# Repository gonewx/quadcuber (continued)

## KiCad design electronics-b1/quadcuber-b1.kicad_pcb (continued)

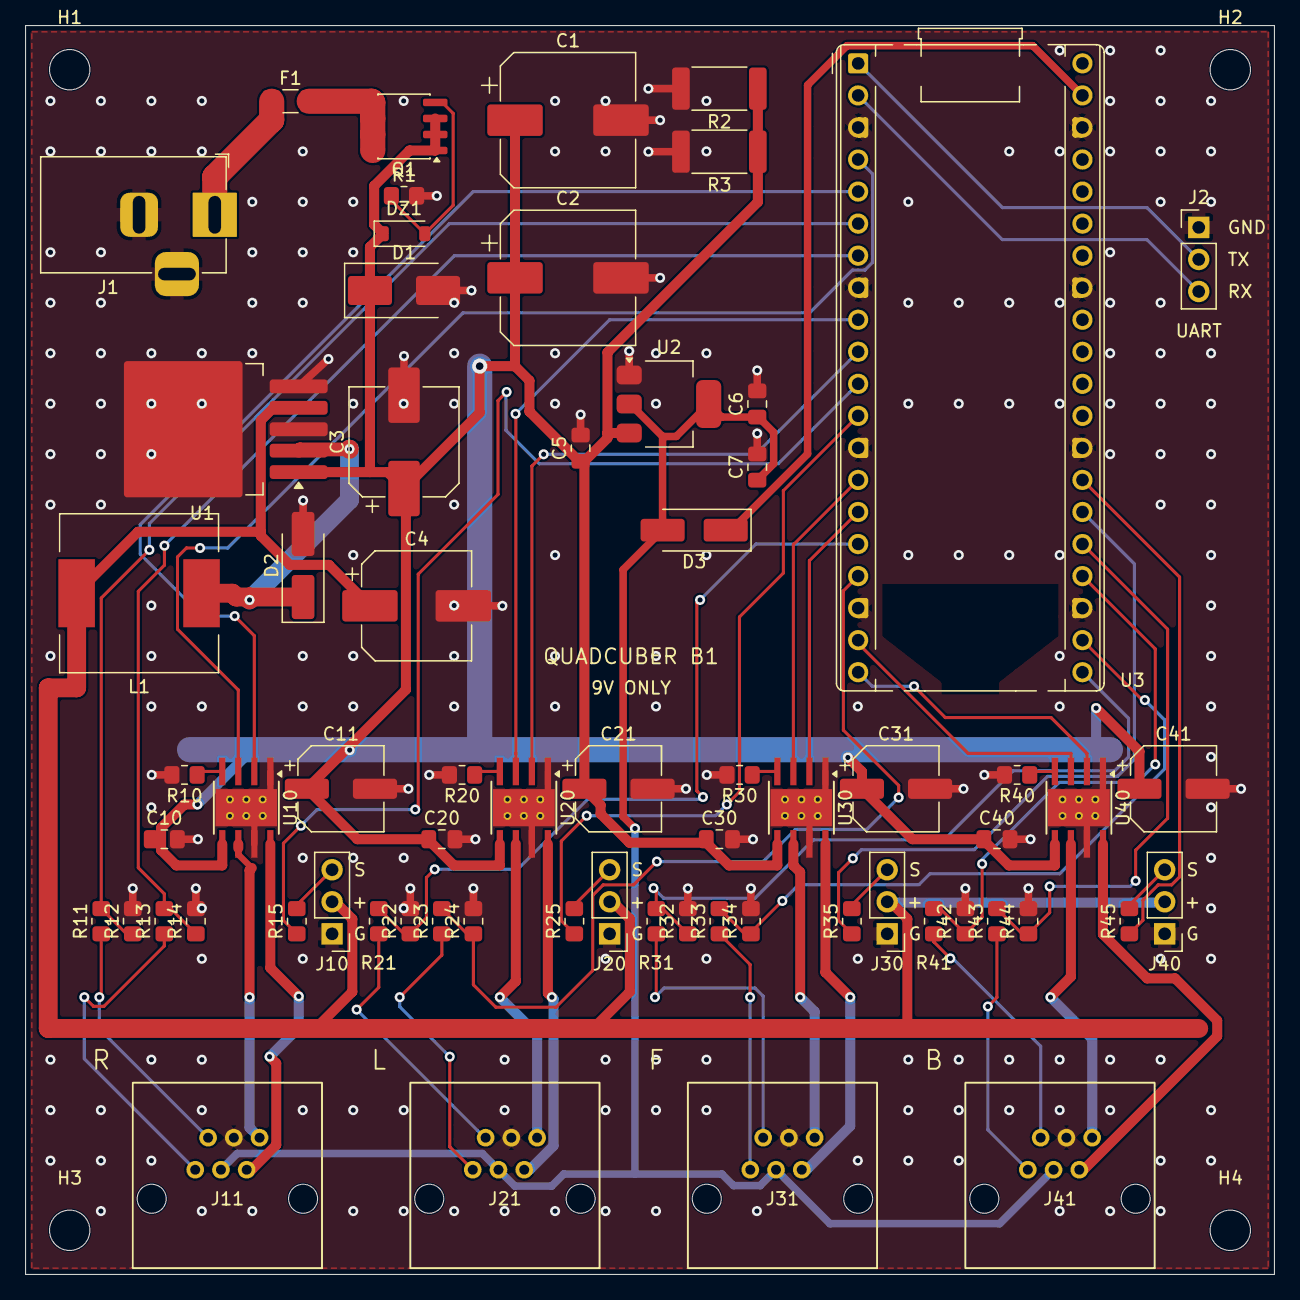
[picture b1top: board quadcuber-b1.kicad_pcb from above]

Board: 2 copper layers, 99.0 x 99.0 mm, 70 parts (0 on the bottom side), 55 nets.

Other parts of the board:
H1, H2, H3, H4: M3; MountingHole_3.2mm_M3

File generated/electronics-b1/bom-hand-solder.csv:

焊接顺序,类别,型号/规格,位号,数量,封装,说明
1,贴片 IC,AMS1117-5.0（SOT-223）,U2,1,SOT-223-3_TabPin2,输入最高 15V；约 0.1A 时功耗约 0.4W
1,贴片 IC,AO4407A P-MOS（-30V/12A，SOIC-8）,Q1,1,SOIC-8_3.9x4.9mm_P1.27mm,反接保护：漏极(5-8)接电源、源极(1-3)接 VM；导通后双向导电
1,贴片 IC,DRV8871DDAR,"U10,U20,U30,U40",4,Texas_HTSOP-8-1EP_3.9x4.9mm_P1.27mm_EP2.95x4.9mm_Mask2.4x3.1mm_ThermalVias,热风枪焊散热焊盘
1,贴片 IC,LM2596S-5.0（TO-263-5）,U1,1,TO-263-5_TabPin3,ON/OFF(5) 接地=常开；FB(4) 接输出；散热片焊盘接地铜
2,贴片电阻电容,0.1u 0.1µF 0805,"C7,C10,C20,C30,C40",5,C_0805_2012Metric_Pad1.18x1.45mm_HandSolder,
2,贴片电阻电容,10k 0805,"R1,R11,R13,R21,R23,R31,R33,R41,R43",9,R_0805_2012Metric_Pad1.20x1.40mm_HandSolder,
2,贴片电阻电容,10u/25V 10µF/25V 0805,C5,1,C_0805_2012Metric_Pad1.18x1.45mm_HandSolder,
2,贴片电阻电容,20k 0805,"R12,R14,R22,R24,R32,R34,R42,R44",8,R_0805_2012Metric_Pad1.20x1.40mm_HandSolder,
2,贴片电阻电容,220 0805,"R15,R25,R35,R45",4,R_0805_2012Metric_Pad1.20x1.40mm_HandSolder,
2,贴片电阻电容,22u/16V 22µF/16V 0805,C6,1,C_0805_2012Metric_Pad1.18x1.45mm_HandSolder,
2,贴片电阻电容,300R 1W 300Ω 1W 2512,"R2,R3",2,R_2512_6332Metric_Pad1.40x3.35mm_HandSolder,
2,贴片电阻电容,43.2kΩ 1% 0805,"R10,R20,R30,R40",4,R_0805_2012Metric_Pad1.20x1.40mm_HandSolder,限流约 1.48A（64/R）
3,贴片二极管,12V BZT52C12 稳压管,DZ1,1,D_SOD-123,阴极(1)接源极 VM，限制 |Vgs|<=12V
3,贴片二极管,SMBJ12A 单向 TVS,D1,1,D_SMB_Handsoldering,阴极(1)接 VM
3,贴片二极管,SS14 肖特基,D3,1,D_SMA_Handsoldering,阴极(1)接 Pico VSYS
3,贴片二极管,SS34 3A 肖特基,D2,1,D_SMA_Handsoldering,阴极(1)接开关节点
4,贴片保险丝,1206 贴片保险丝 8A 慢断,F1,1,Fuse_1206_3216Metric_Pad1.42x1.75mm_HandSolder,只防短路起火，不限流
5,贴片电解电容,100u/25V 100µF/25V 贴片电解 6.3×7.7,"C11,C21,C31,C41",4,CP_Elec_6.3x7.7,
5,贴片电解电容,220u/25V 220µF/25V 贴片电解 8×10.5（输入）,C3,1,CP_Elec_8x10.5,
5,贴片电解电容,470u/16V 470µF/16V 贴片电解 8×10.5（输出）,C4,1,CP_Elec_8x10.5,
5,贴片电解电容,470u/25V 470µF/25V 贴片电解 10×10.5,"C1,C2",2,CP_Elec_10x10.5,
6,贴片电感,33uH 3A 33µH/3A 贴片功率电感 12×12,L1,1,L_12x12mm_H8mm,
7,排针/排母,UART G TX RX 1×3 排针,J2,1,PinHeader_1x03_P2.54mm_Vertical,接 Zero W：GP0=TX、GP1=RX
7,排针/排母,树莓派 Pico H + 2×1×20 排母,U3,1,RaspberryPi_Pico_Common_THT,USB 朝上；排母两排相距 17.78mm
7,排针/排母,舵机 B S+G 1×3 排针,J40,1,PinHeader_1x03_P2.54mm_Vertical,自下而上 G/+/S
7,排针/排母,舵机 F S+G 1×3 排针,J30,1,PinHeader_1x03_P2.54mm_Vertical,自下而上 G/+/S
7,排针/排母,舵机 L S+G 1×3 排针,J20,1,PinHeader_1x03_P2.54mm_Vertical,自下而上 G/+/S
7,排针/排母,舵机 R S+G 1×3 排针,J10,1,PinHeader_1x03_P2.54mm_Vertical,自下而上 G/+/S
8,插座,9V DC 中心正 DC-005 5.5/2.1mm,J1,1,BarrelJack_Horizontal,脚1=中心(+)、脚2=外壳(-)、脚3=开关脚并地；焊前用实物核对孔位
8,插座,EV3 B 同批 EV3 插座（用户已有）,J41,1,EV3_Socket_UserDrawing,针序未用实物核实：接电机前断电六路通断
8,插座,EV3 F 同批 EV3 插座（用户已有）,J31,1,EV3_Socket_UserDrawing,针序未用实物核实：接电机前断电六路通断
8,插座,EV3 L 同批 EV3 插座（用户已有）,J21,1,EV3_Socket_UserDrawing,针序未用实物核实：接电机前断电六路通断
8,插座,EV3 R 同批 EV3 插座（用户已有）,J11,1,EV3_Socket_UserDrawing,针序未用实物核实：接电机前断电六路通断

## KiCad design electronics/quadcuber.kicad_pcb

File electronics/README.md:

# 四臂集成单板控制器 A1（板载RP2040） — 工程评审，未制造放行

> 当前手焊装配使用 [B1 底板](../electronics-b1/README.md)，请看 [B1 焊接与首次上电指南](../docs/b1-soldering-guide.md)。下文与本目录文件仅描述旧 A1 集成板，不适用于 B1。

本目录是 A1 电子源目录。打开 `quadcuber.kicad_pro`，包含原生可编辑原理图和四层 PCB、本地符号/封装库。本设计为**单块PCB，RP2040、QSPI Flash、晶振、USB-C、驱动和电源均直接焊接在板上**；A0的Pico H插装已移除。马达使用EV3裸插座。接线定义仍从 `../wiring/spec.py` 导入，固件未改动，也没有把 R/L 固件描述成已支持四臂控制。

**A1 历史工程首板入口：[送厂包与分工](../generated/electronics/engineering-first-board/README.md)。** 设计基线 `3cfff7c`（相对 `db20b98` 只把风险丝印改为 `PROTOTYPE` / `VERIFY EV3 PINMAP BEFORE MOTOR USE`）、J1为RASPC722X DC5521；嘉立创双面SMT共153件（J5含4个PTH屏蔽脚补焊待厂商确认），用户自焊18件通孔器件。39个型号已填LCSC编号；U7 W25Q16RVCNJQ与F10–F13 MF-MSMF110/16X-2未上架，须代购或寄料。本包供受控首板CAM审核，未宣称厂商已接受或量产/实板性能通过；提交时附CAM确认单。旧Phoenix与所有 `ENG-FULL-*` / `ENG-POWER-CONTROLLER-*` 文件只供历史审查，不得下单混用。

EV3仍以用户尺寸图及同批实物为依据，不索取不存在的完整MPN文件，不替换普通RJ12。首板承担孔位/主体适配返工风险；连接电机前必须做六路断电通断及机械试配，触点电流能力由受控实验建立。C26/C36不装。首次上电与逐级扩大负载条件见首板包，不要求首板尚未制出时已有实板动态测试结果。

## 已批准的BOOT与反馈修订

当前修订删除R20/R30，使100nF C22/C32直接跨接各自BOOT–SW；反馈保持100k/13.3k，改为RT0603BRD07100KL/RT0603BRD0713K3L（0.1%）。这是实物源电路、原理图、PCB、BOM和仿真输入的同步修改，旧49.9Ω仿真记录仅作为历史证据。[实施和验证记录](../generated/electronics/boot-direct-revision/README.md)保存布局改进、实际测试结果及未覆盖风险。未作量产性能放行；精度升级不等于已证明温漂及瞬态全程满足5.25V。工程首板的CAM入口与试验边界以上述唯一包为准。

## KiCad版本与显示

已使用用户批准的官方 **KiCad 10.0.7 Lite** 完成PCB与全部12张原理图的原生 `upgrade --force` 重存，以及ERC、含schematic parity的DRC和引脚契约复验。通过原生pcbnew API把原理图已有的MPN/Manufacturer同步为PCB隐藏字段，解决10版新增的198个缺失MPN一致性告警；未屏蔽检查。Lite本身缺少标准3D库；本轮已把实际使用的模型归档在工程内并以`${KIPRJMOD}`关联，171个已装配器件均有显示。蓝色插座主体和橙色110/16X保险是有来源的简化包络，F2/F3与L1/L2也采用按公开尺寸独立生成的简化包络（原厂CAD再分发许可未确认），不能称为整板精确3D验证；详见[显示修复报告](../generated/electronics/3d-display-repair/README.md)。C26/C36保持DNP并默认隐藏模型。

二维编辑器的红/褐色铜区和其他图层配色不是实物阻焊颜色。查看实物外观用“视图→3D查看器”（Alt+3）；成品绿色阻焊应在最终制造规格中明确。带Pico双排插座、丝印A0的板图是旧版；本目录A1采用直接焊接RP2040，打开时应核对丝印及工程路径。

## 交付入口

- [KiCad工程](quadcuber.kicad_pro)、[原理图PDF](../generated/electronics/schematic.pdf)
- [整板3D斜视](../generated/electronics/3d-display-repair/board-oblique.png)、[模型来源和限制](lib/3dmodels/README.md)、[当前显示修复核验](../generated/electronics/3d-display-repair/verification.json)
- [正面板图](../generated/electronics/pcb-top.png)、[反面铜图（顶视透视）](../generated/electronics/pcb-bottom.png)、[正面装配图](../generated/electronics/assembly.png)、[反面装配图（顶视透视）](../generated/electronics/assembly-bottom.png)
- [汇总电子BOM](../generated/electronics/bom-grouped.csv)、[逐件BOM](../generated/electronics/bom.csv)、[贴装坐标](../generated/electronics/positions.csv)
- [ERC](../generated/electronics/erc.rpt)、[DRC](../generated/electronics/drc.rpt)、[状态与源哈希](../generated/electronics/release-status.json)、[独立复核](../generated/electronics/independent-review.md)
- [唯一工程首板Gerber/钻孔、SMT BOM/CPL、自焊清单与CAM单](../generated/electronics/engineering-first-board/README.md)。旧 `fabrication-preview-NOT-RELEASED` 为原始审核输出，不单独作为订单交付。

正反面SVG/PNG沿同一KiCad顶视坐标系绘制，便于对照；实际从板底观察时需镜像，不可用透视图推断插座针序。

TP测试焊盘和安装孔是PCB内建特征，采购数量记为0；可选电容的DNP原因单独列在BOM备注中。

## 电源仿真状态

已保留[65个简化ngspice边界工况及热敏感性计算](simulation/README.md)，以及[108个保护/RLC/能量工况](../generated/electronics/protection-analysis/report.md)。它们不等于芯片动态验证。本轮已取得TI未加密TPS54302原厂模型，执行9个真实双路BOM输入/电容工况，但均在0.458～0.779ms因数值问题中止，**0个完整完成、0个通过，负载阶跃尚未执行到**。见[原厂模型报告、部分波形与日志](../generated/electronics/simulation/buck-vendor/report.md)。当前阻塞已从下载变为ngspice动态兼容；制造HOLD保持。[确切料号审查](sources/bom-exact-part-audit.md)仍记录原厂已核与未决项。

## BOM选型标准

同等电气、散热、供应与装配条件下，**默认优先贴片元件**，以缩短回路、降低高度并便于机器装配。先核确切原厂料号、封装/引脚、生命周期，再按实效电容、脉冲能量、持续/RMS电流及局部温升留余量；不能用芯片峰值额定充当整板持续额定。常用低功耗器件优先0603/0805，小封装只在布线/去耦确有必要时使用，功率器件按载流与散热选择尺寸。

连接器优先兼容、插拔固定及足够触点电流；大电容同时比较容量、纹波、寿命、体积和高度，不能只因“贴片”而牺牲性能。当前大多数器件已是贴片，大电解/布局仍可研究紧凑化；144×112mm是当前工程版外形，**并未证明已优化到最小**。本轮保持机械外形，先完成确切料号与保护闭环。原厂已核、渠道生命周期和仍未知的证据层级见[完整BOM审查](sources/bom-exact-part-audit.md)。

## 架构与器件

- **控制器：裸RP2040 QFN56+EP**。保留GPIO0～21、8个PIO状态机、12MHz时钟、2MiB Flash以及GP25指示灯，使用基于RPI_PICO的QUADCUBER_A1 MicroPython UF2，无需迁移MCU平台。GP22/23/26～29未用；GP24为USB VBUS分压检测。ROM BOOTSEL、RUN复位、UART和SWD均直接引出；SWD口3V3为参考电压，禁止外部注入供电。
- **Flash：W25Q16RVCNJQ**，CN 150mil SOP8，原厂在产替代，保留3.9mm窄体焊盘。使用[QUADCUBER_A1启动配置](firmware/README.md)，在现有MicroPython/Pico启动代码上修正QE位判断，避免RV状态寄存器差异造成反复写入；仍通过USB UF2烧录。选型、供货及逐命令兼容证据见[Flash复核](sources/flash-selection-review.md)。
- **12MHz ABM8-272-T3**，CL10pF、两颗15pF、XOUT串1k；RP2040每个电源脚配置100nF，内部稳压输入/输出各1µF。3.3V接IOVDD/ADC_AVDD/VREG_IN/USB_VDD；VREG_OUT仅接1.1V DVDD，TESTEN及EP接地。
- **USB4105-GF-A** USB-C USB2从设备，CC1/CC2各独立5.1k，下游数据通过USBLC6-2SC6和27Ω串阻。GCT原厂图与库的定位孔、壳脚槽和针序逐项核对；没有USB PD，也不向主机提供VBUS。

- **四路 DRV8871DDAR**，每马达一颗，HTSOP-8 PowerPAD，热焊盘接地、有原厂推荐热孔。IN1/IN2 真值表与现有慢衰减 PWM 一致，00滑行/休眠、01反转、10正转、11刹车。现有20 kHz PWM符合器件范围；休眠后首次唤醒最多50 µs，样机须重测低速定位。不沿用 DRV8833 名义模块电流：DRV8833 PWP/RTY 每桥1.5 A RMS，而PW只有0.5 A，且10.8 V推荐上限不利于9 V母线回灌。DRV8871的6.5～45 V供电裕量更合适，**3.6 A只是峰值，不是整板持续额定**。
- 每桥 **43.2 kΩ ±1%**，64 kV/R 名义1.481 A；按59～69 kV及电阻容差推算1.352～1.613 A。该门限不是所有PWM/电感工况下的精密峰值保证。9 V EV3大马达原厂堵转1.8 A，因此设计有意限流降低堵转扭矩，带载夹持须验证。
- **两路 TPS54302DDCR**，5 V基准电路，R上100k/下13.3k、10µH电感、双22µF/25V输出及75pF前馈（C26/C36可选470µF默认DNP，须验证环路后才装）。每路带两个舵机，A路还带编码器与RP2040。电感 **SRP1245A-100M** 为10µH、9 A RMS、16 A饱和额定，避免饱和电流低于控制器6 A故障限流上界。芯片3 A额定不等于封闭机箱持续3 A；设计负载预算见下。
- **八路 SN74LVC2G17 施密特整形**：每输入1k串联、100k下拉，5 V容限、3.3 V供电。替代旧10k/20k分压，避免5 V边缘直接到RP2040；不反相、保持`ENC_PULLUP=False`，PIO资源不变。器件Ioff保证断电输出不会把编码器5 V送入3.3V供电。马达pin4由独立0.5 A PTC保护的5V_ENC供电。
- 舵机每路**MF-MSMF110/16X-2、16 V、1.1 A PTC**（替代已淘汰6 V旧型号）、**SN74AHCT1G125**（由该路PTC后供电）、220Ω输出串阻、GPIO及输出下拉。3.3 V输入符合TTL阈值；原厂输入漏电在VCC=0时也有规格，避免USB-only的高GPIO经舵机信号反向供电。此处不声称输出端可任意外灌电压；不接外部5 V到舵机端口。

## 电源、回灌与默认态

J1采用 **Switchcraft RASPC722X**，配5.5/2.1 mm中心正插头（官方配762/762Z、筒长9.5 mm），只接**稳压9 V ±2%直流电源**，设计以≤5 A首板连续输入预算、8 A入口保险为边界。sleeve shunt不接线；推荐三槽孔、父线程图面核验来源及原件待归档状态见[入口候选审查](sources/raspc722x-review.md)。厂家5 A carrying额定不取代首板连续温升验证，8 A保险不构成5 A限流。不能接12 V，也不能接未评估的3串锂电。外部电源应有限流功能，动力断开应通过入口物理开关/拔电；USB仅用于逻辑和烧录，不能带动电机、舵机。

入口为已纠正的**0407008.WR、8 A/24 VDC时滞保险**（407系列，1206专用焊盘）、LM74700QDBVRQ1+CSD18540Q5B理想二极管。MOS源极接VIN_FUSED、漏极及大焊盘接VM；LM74700的VCAP电容跨VCAP和ANODE，不能误接到地。保护反极性、阻止VM倒流到电源，避免串联肖特基8 A时约4.26 W的发热。**EN不是正向断电开关**，体二极管仍可供电；该电路也没有浪涌限流。

输入SMBJ12CA吸收正负瞬态，输出SMBJ12A吸收回灌脉冲。输出TVS的12 V是反向工作电压，不是钳位电压；额定脉冲钳位19.9 V，相对于驱动45 V、降压28 V和VM电容25 V有裕量，但必须实测布线寄生尖峰。TVS不适合持续消耗制动功率，也不保护电机不受任何过压：只允许9 V供电，禁止持续外力反拖。控制应以慢衰减刹车优先，回灌测试必须观察VM、电机端、电源端与TVS温升。

母线六只470µF/25 V共2820µF，储能9→12 V约0.0888 J，9→13.3 V约0.135 J；它不是四马达机械动能的保证。新增R500/R501，两只300Ω/1W并联为150Ω母线泄放，9.18 V时总耗散约0.562 W，给重复小能量回灌提供确定的放电路径。暂定**整板每次回到母线的总能量≤0.05 J、频率≤5 Hz、脉宽5～100 ms**，此范围的简化模型最高VM11.204 V且不进入TVS雪崩；实际机械能仍须验证。该泄放不是大功率制动器，也不允许持续反拖。首次上电和热插拔也要核验电容浪涌与保险I²t。F1名义熔断I²t为24.12 A²s，不是保证最小值或总开断能量；分断能力60 A@24 VDC，不能用于无限短路容量的电池。时滞保险不保护半导体快速故障，外部9 V电源必须具备短路限流。没有把旧R空载实测当作这块新驱动板的试验结果。

5V_A经D2（SS14），USB VBUS经F3（0.5A PTC）和D5（SS14），分别单向汇入VSYS，再由TLV75533PDBVR产生3.3V。两路源的阳极独立、阴极均接VSYS，外部5V不能直接进入USB VBUS。USBLC6的上保护轨接VSYS、就近100nF，避免外供电时DP上拉经ESD导向二极管绕过D5回灌VBUS。所有GND共地，USB地不承担动力回流。

GP24的100k/100k分压用于遥测。Stock TinyUSB通常强制认为VBUS存在，分压本身不会关闭USB上拉；断电主机的数据脚输入保护路径尚须验证，因此不声称通过USB规范或零微安回流认证。首板须分别测VBUS及DP/DM对断电主机的电压/电流。USB仅给逻辑供电，F3不构成USB枚举电流协商。

TLV755的500mA是芯片额定，本板逻辑3.3V连续预算≤150mA。DBV封装按TI给出的231.1°C/W估算：VSYS约4.7V、150mA时0.21W、约49°C温升，40°C环境约89°C结温；这只是估算，首板必须测满负载与最高环境温度，不能套用其他封装的热阻。

输入下拉令RP2040未启动/复位时电机00、舵机无脉冲。供电瞬态下舵机内部仍可能抖动，PTC不会瞬时切断精确电流，驱动自动热恢复也不是锁存式急停。固件原有未标定锁定保持不变。

## 负载与热边界

四电机同时到名义限流约5.92 A；四只灰色270°Geekservo原厂标称堵转各700mA，总2.8 A@5 V（原厂没有给测试电压和容差，不是保证上限）。另按逻辑/编码器0.25 A@5 V、降压效率85%估算，输入约7.91 A，已经接近8 A保险，**不允许把全堵转当持续工作模式**。设计正常工况预算：马达各≤0.75 A RMS作为首板热验证目标、两个5 V支路各≤1.5 A持续（A路包含逻辑预算），两路5 V同时1.5 A时加泄放负载合计约5.02 A，需稍降负载以满足入口≤5 A；短时峰值和温升须实测。PTC1.1 A是25°C保持电流，热环境下降额，不能用它来承诺舵机启动上限。

DRV8871在1 A时以0.565Ω典型桥阻估算0.565 W；升温后桥阻上升，1.48 A时仅导通损耗即约1.24 W。TI 41.1 K/W是规定测试板结果，不能直接当本板热阻。每颗留独立散热区域，热焊盘/热孔/地铜必须焊接完整；环境40°C下目标结温<125°C，需同时四路负载热测确认。若达不到，应降连续电流/占空比或增加散热，不能提高限流电阻之外的额定宣传。

入口J1→F1→Q1源极设宽铜区，Q1漏极以12颗Ø0.4 mm过孔连接VM内平面。DRV每颗6个原封装热孔接地，VM及PGND增加并联过孔；上下层地铜与内层地面共同散热。实际铜区需结合样机温升核验，不把理想走线公式当额定。两颗主输入10µF置于降压芯片背面近旁，以0.8 mm短线接邻近VIN/GND孔，最长1.956 mm；记录见`buck-loop.json`。

## 板形、装配与机械安装

144×112 mm矩形，四个Ø3.2 NPTH孔，坐标(4,4)、(140,4)、(4,108)、(140,108)，孔距136×104 mm均为8 mm网格。四个34 mm臂单元（J10为避开左安装孔额外右移1 mm）容纳12.2×15 mm插座主体和至少15.3 mm固定耳预留宽度、直插线缆、舵机排针、驱动散热区；上部为USB-C及板载RP2040最小系统、两套降压和电源入口。小于这一宽度会挤占接口及功率单元余量，因此没有沿用洞洞板尺寸。

它不是直接卡入现有乐高销孔的板。通过**新增绝缘托架**底挂，主要元件面朝下，反面（含C20/C30输入电容、RP2040去耦及USB供电二极管）基板表面置于模型Y=124 mm；X/Z以机器人中心为板中心。LDraw Y朝下，模型全机最大Y=116 mm；独立审查扫描臂0..355°每5°及开/合两端、支承0/20.4/40.8 mm，下方8 mm空隙成立。**这只证明裸基板与模型分离，不证明托架、反面电容、紧固件、线缆或公差完成安装验证**。

**双面装配**：C20/C30、RP2040去耦和USB供电D5等位于B.Cu；反面朝机器人，必须从8 mm净距中扣除反面最高器件的实际最大高度、焊脚及装配公差，不能把8 mm称为器件净空。最终双面装配以`positions.csv`的Side列及反面装配图为准。

需新增足够高度的脚及底部防护，按最高电容、双面器件高度、焊脚剪切和至少5 mm防护空隙确定，初始为板上方8 mm、板下约25 mm及防护的40 mm级抬高预算。托架机械设计未冻结，因此不能声称机械集成已完成。USB一侧留至少15 mm插拔空间，马达口外预留25 mm直出区再弯线，按实际线材弯曲半径调整；不将未确认的线长写成BOM事实。舵机口丝印G/+ /S，**棕/黑GND，中间红+5 V，信号S**；排针本身无防呆，插前按实际线序确认。

## 重建与编辑

已安装/使用官方KiCad 10.0.7 Lite和其Python 3.11 pcbnew；外部布线工具从[Freerouting官方v2.1.0发布](https://github.com/freerouting/freerouting/releases/tag/v2.1.0)下载。无需购买模块、运行云端EDA或迁移固件。

```sh
# 如环境HOME只读，可把XDG配置/缓存指向可写临时目录（build.py已自动处理）。
export XDG_CONFIG_HOME=/tmp/quadcuber-kicad/config
export XDG_CACHE_HOME=/tmp/quadcuber-kicad/cache
export XDG_DATA_HOME=/tmp/quadcuber-kicad/data
# 本环境的官方Lite AppImage解包入口；其他安装可改为自己的路径。
export KICAD_APP_RUN=/workspace/tools/kicad-10.0.7/squashfs-root/AppRun
# 或分别设置KICAD_CLI（可执行文件路径）和KICAD_PYTHON（Python命令，可含参数）。
# 普通系统安装不设上述变量：使用PATH内kicad-cli和当前Python。
# CLI及pcbnew均须为10.0.7，版本不符立即报错。
# 正常编辑：直接用KiCad编辑原理图/PCB，再导出验证。
python3 electronics/build.py
python3 electronics/check.py
# 对比冻结的迁移前基线与当前板的几何/网表（不修改设计）。
"$KICAD_APP_RUN" python3.11 electronics/verify_kicad10_migration.py
python tools/build_distribution.py
python -m unittest tests.test_wiring tests.test_arm_selection tests.test_firmware tests.test_repository_layout -q

# 仅重建原理图/BOM，不动已布线PCB：
/usr/bin/python3 electronics/generate.py --metadata-only
# 从零研究布局才运行以下命令；它会覆盖已布线PCB，并不重现最终走线。
/usr/bin/python3 electronics/generate.py
```

`build.py`使用现存KiCad源，不会重置布局。标准输出唯一位于`generated/electronics/`：BOM、网表、SVG/PDF原理图、板图、ERC/DRC、制造预览文件、审查状态。`generate.py`与`circuit.json`中的坐标是初始布局，最终位置和双面装配以native PCB及其导出的`positions.csv`为准。自动布线结果可能不同，控制器由update_controller.py重新放置背面去耦并建立In2局部3V3岛；其操作会删除该区域走线，不能当普通导出步骤。控制器细间距扇出、去耦朝向和局部地回流已在native PCB中进一步修正；辅助布局脚本仅用于重新研究布局。In1始终保留完整地参考，In2只在控制器局部允许少量信号与1.1V出线，VM功率区不作信号通道。后处理脚本含历史A0特定废线清理；重新布线后必须重新审查并修正，而不是保证一键得到相同铜形。只有native PCB是最终布线事实；`generate.py`保存可重做初始布局的方法，不承诺重现自动布线每个拐点。

## 实际验证记录

本次正式导出：ERC 0错误/0警告；包含原理图一致性检查的DRC 0违规、0未连接、0封装错误；543个已连接符号引脚与PCB的网络契约核对为0错误。报告和源哈希见交付入口。历史独立审查`generated/electronics/independent-review.md`绑定迁移前KiCad 9 PCB哈希，不能作为当前10版文件已被重新独立审查的证明。当前迁移证据见`generated/electronics/kicad10-migration.json`及本次重新导出的报告；迁移前后器件位置、焊盘尺寸/钻孔/网络、走线与过孔、铜区轮廓和实填铜、板框均相同。J5两个无编号NPTH的层掩码由10版原生保存规范化为全部铜层（孔位与孔径不变），物理几何比较明确归一此项。本次再次执行既有接线/R-L选择/固件与仓库布局回归；按仓库命令`python tools/build_distribution.py`补建分发产物后，相关51项与仓库布局8项合计**59项全部通过**，没有修改测试断言；这不等同四臂软件或PCB实物通过。

## 放行清单

1. **EV3实物针序与项目工作边界**：孔位及1/6标注已按用户图落实；不再索要不存在的更多资料。完整EV3板制板前仅需同批样品一次六路断电通断记录及观察方向，避免镜像/错序；触点电流、压降、温升与机械试配在受控样板上建立限定边界，不冒充厂家额定。如映射改变，更新封装网络并重跑ERC/DRC。NO-EV3台架变体单独标识，不替代完整设计。
2. **电源/热原型**：9 V台式电源限流，从无马达到单路负载再四路，测5 V启动、负载跃变、编码器波形和20 kHz电机电流；禁长时堵转。验证TVS能量、VM瞬态、铜温、驱动结温估算、输入保险及PTC降额。
3. **控制器与USB组合**：首次按住BOOTSEL插USB，确认ROM盘枚举及QUADCUBER_A1 UF2刷写；RUN复位、SWD读写、12MHz时钟、1.1/3.3V启动、QSPI读写及编码器/舵机默认态。USB-only、9V-only、两者同时、动力掉电/恢复，确认无反向供电、复位失控或异常舵机脉冲。
4. **机械**：托架与脚、USB/马达插拔、线缆运动包络、反面绝缘、安装螺钉不触铜、USB插头与BOOTSEL/RUN按键可达性。
5. **制造**：板厂确认4层1.6 mm，外铜2 oz/内铜1 oz，RP2040细间距和USB差分阻抗需板厂复核，逻辑最小0.15 mm线宽/间距（其余网络0.20 mm），USB连接器原厂孔到焊盘间隙按专用0.18 mm规则，最小0.30 mm成品孔；驱动热孔工艺和锡膏分窗按TI，检查焊孔与排针实际料样。当前没有做过PCB实物测试。

## 资料与许可证

详细依据见 `sources.md`。本地拷贝KiCad标准封装来自本环境KiCad9库，遵守[KiCad Libraries License](https://www.kicad.org/libraries/license/)的CC-BY-SA4.0及PCB设计例外；RP2040封装保留原厂焊盘并将EP热孔改为Ø0.30/焊盘Ø0.60 mm，以匹配板厂工艺；EV3自建封装明确标注未核部分。不把公开资料的缺失字段编造成制造商规格。

旧 `python electronics/package_review.py` 仅生成历史审查汇总到 `output/electronics/`，会包含历史变体，不能用作当前送厂资料。当前首板只能使用 [engineering-first-board 唯一入口](../generated/electronics/engineering-first-board/README.md)，由 `electronics/package_first_board.py` 生成并校验源哈希。

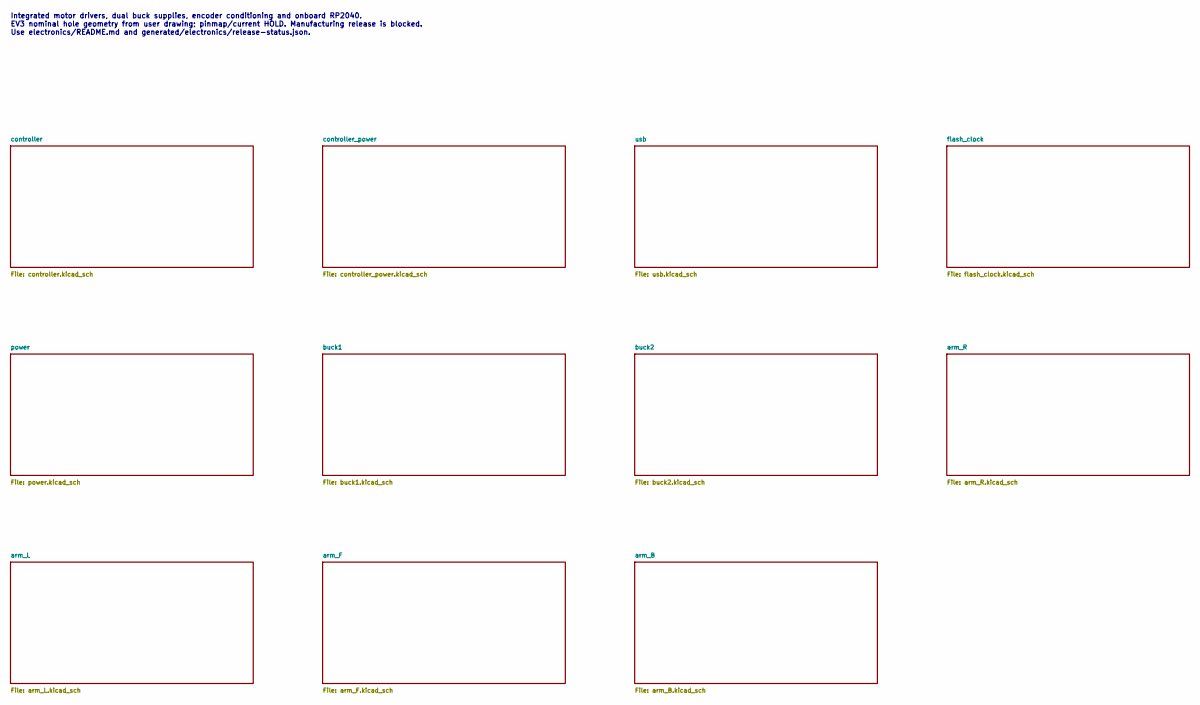
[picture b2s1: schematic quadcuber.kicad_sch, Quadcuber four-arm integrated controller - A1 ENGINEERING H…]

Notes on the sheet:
Integrated motor drivers, dual buck supplies, encoder conditioning and onboard RP2040. EV3 nominal hole geometry from user drawing; pinmap/current HOLD. Manufacturing release is blocked. Use electronics/README.md and generated/electronics/release-status.json.

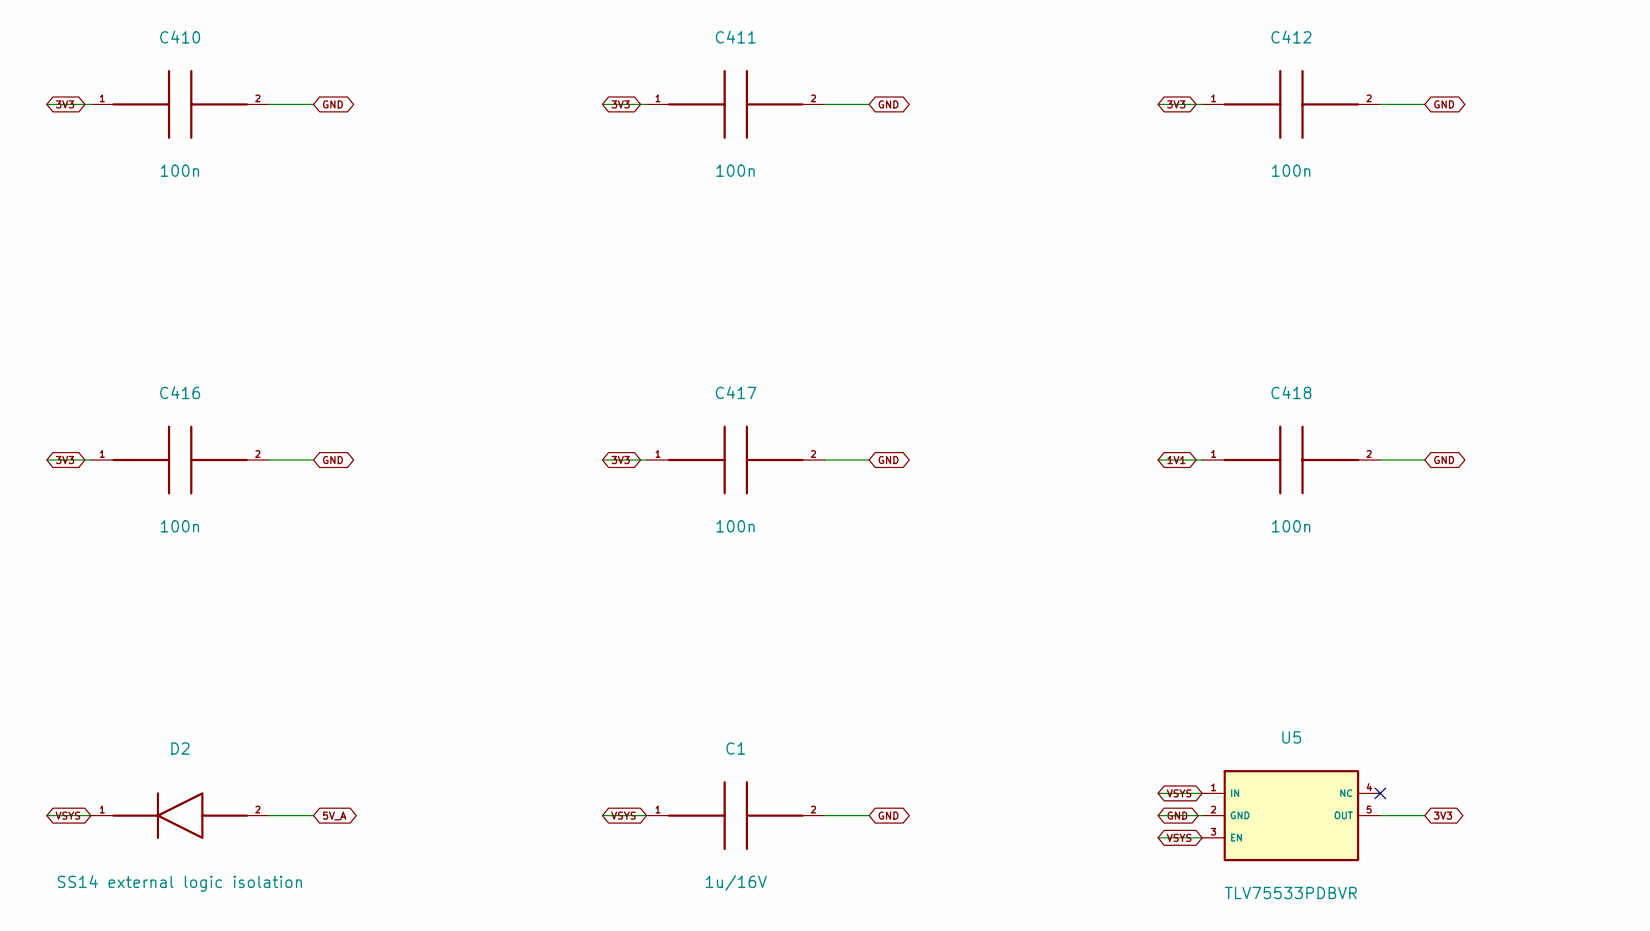
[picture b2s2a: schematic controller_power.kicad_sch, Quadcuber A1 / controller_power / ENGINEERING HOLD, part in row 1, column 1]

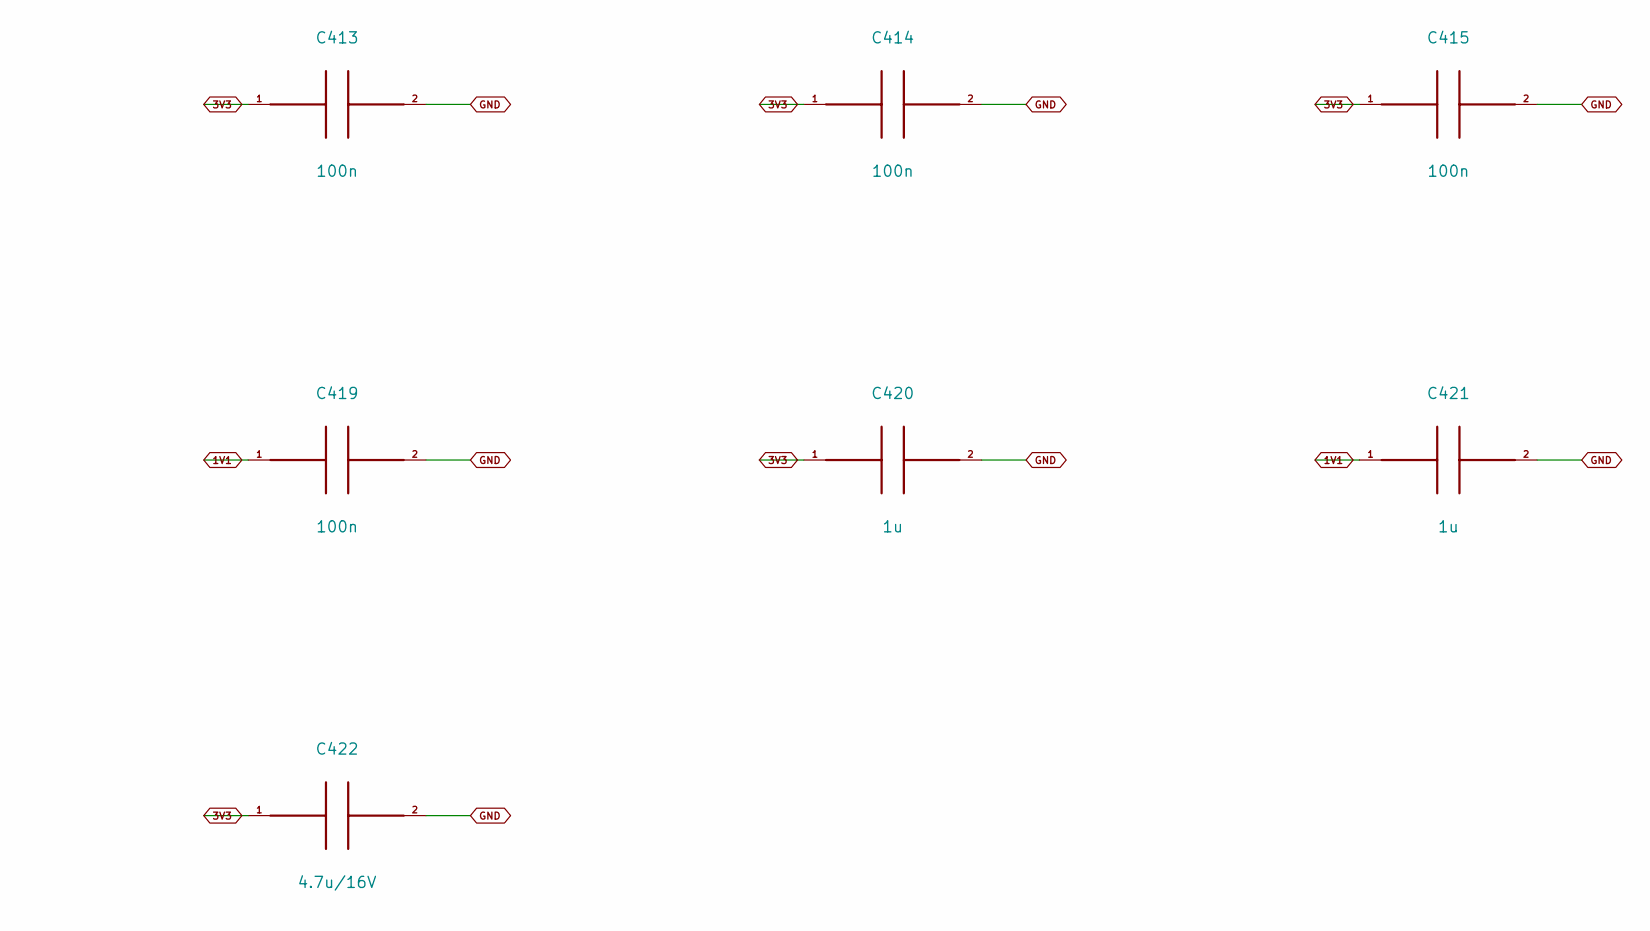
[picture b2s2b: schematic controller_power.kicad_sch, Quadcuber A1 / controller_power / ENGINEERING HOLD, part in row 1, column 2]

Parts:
C1: 1u/16V; C_0805_2012Metric; MPN GRM21BR71C105KA01L
C410, C411, C412, C413, C414, C415, C416, C417, C418, C419: 100n; C_0402_1005Metric; MPN GRM155R71C104KA88D
C420, C421: 1u; C_0402_1005Metric; MPN GRM155R61C105KA12D
C422: 4.7u/16V; C_0805_2012Metric; MPN C0805C475K4PACTU
D2: SS14 external logic isolation; D_SMA; MPN SS14-E3/61T
U5: TLV75533PDBVR; SOT-23-5; MPN TLV75533PDBVR

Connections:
1V1: C418.1, C419.1, C421.1; also elsewhere on the board
3V3: C410.1, C411.1, C412.1, C413.1, C414.1, C415.1, C416.1, C417.1, C420.1, C422.1, U5.5 (OUT); also elsewhere on the board
5V_A: D2.2 (A); also elsewhere on the board
GND: C1.2, C410.2, C411.2, C412.2, C413.2, C414.2, C415.2, C416.2, C417.2, C418.2, C419.2, C420.2, C421.2, C422.2, U5.2 (GND); also elsewhere on the board
VSYS: C1.1, D2.1 (K), U5.1 (IN), U5.3 (EN); also elsewhere on the board

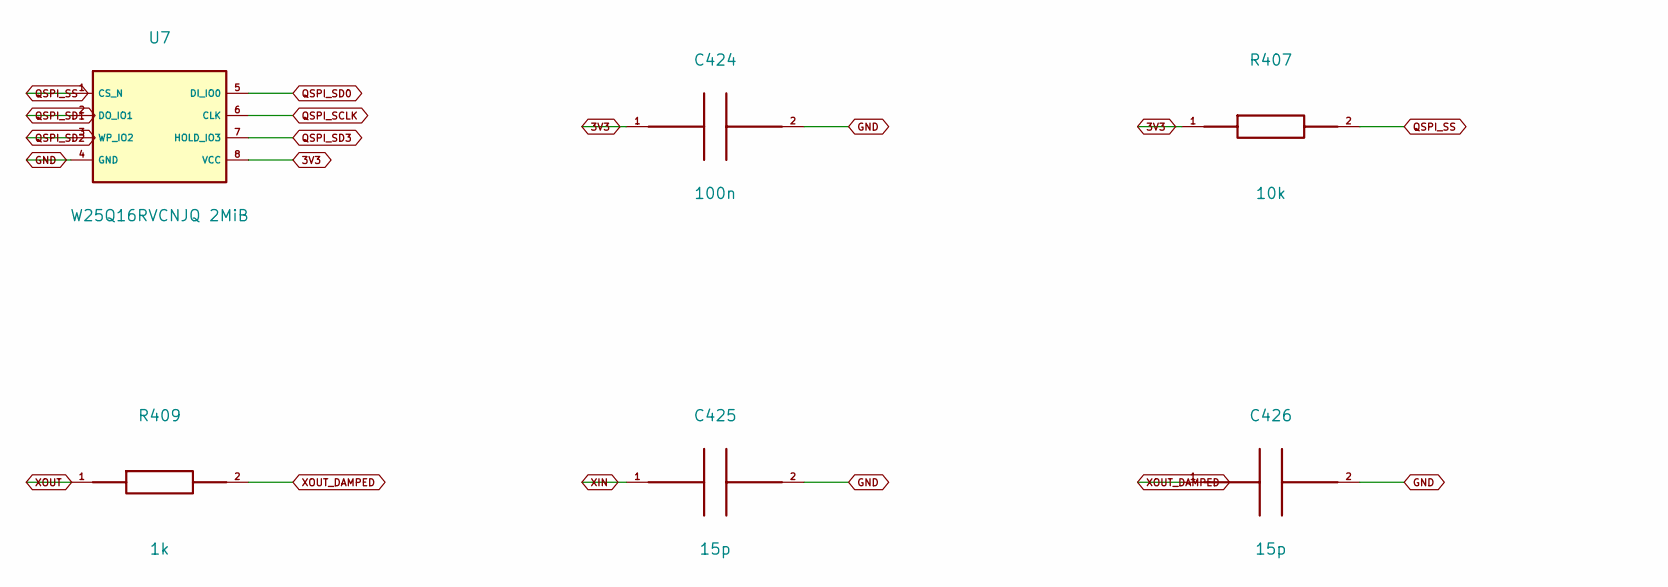
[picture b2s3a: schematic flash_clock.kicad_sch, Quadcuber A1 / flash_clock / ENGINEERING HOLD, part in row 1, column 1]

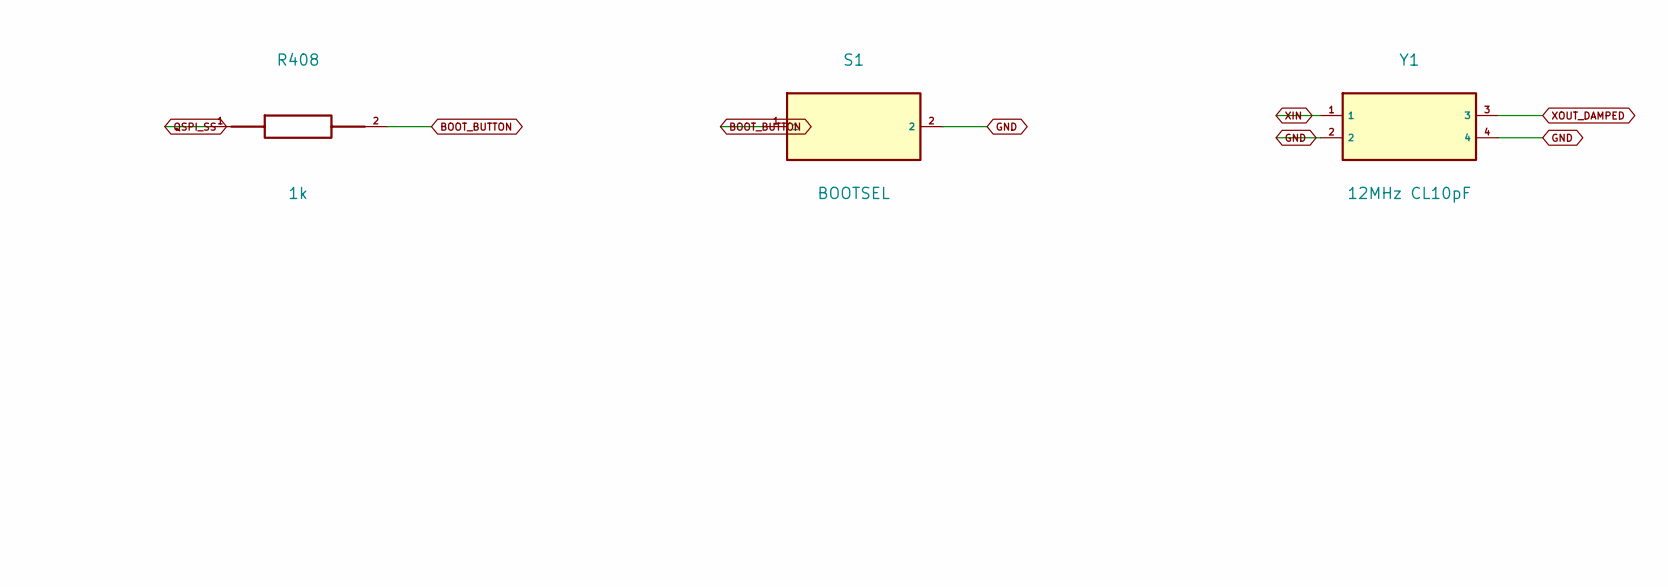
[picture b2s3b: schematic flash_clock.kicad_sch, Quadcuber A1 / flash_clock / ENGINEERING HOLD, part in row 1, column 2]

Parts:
C424: 100n; C_0402_1005Metric; MPN GRM155R71C104KA88D
C425, C426: 15p; C_0402_1005Metric; MPN GRM1555C1H150JA01D
R407: 10k; R_0603_1608Metric; MPN RC0603FR-0710KL
R408: 1k; R_0603_1608Metric; MPN RC0603FR-071KL
R409: 1k; R_0402_1005Metric; MPN RC0402FR-071KL
S1: BOOTSEL; SW_SPST_TL3342; MPN TL3342F160QG
U7: W25Q16RVCNJQ 2MiB; SOIC-8_3.9x4.9mm_P1.27mm; MPN W25Q16RVCNJQ
Y1: 12MHz CL10pF; Crystal_SMD_3225-4Pin_3.2x2.5mm; MPN ABM8-272-T3

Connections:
3V3: C424.1, R407.1, U7.8 (VCC); also elsewhere on the board
BOOT_BUTTON: R408.2, S1.1
GND: C424.2, C425.2, C426.2, S1.2, U7.4 (GND), Y1.2, Y1.4; also elsewhere on the board
QSPI_SCLK: U7.6 (CLK); also elsewhere on the board
QSPI_SD0: U7.5 (DI_IO0); also elsewhere on the board
QSPI_SD1: U7.2 (DO_IO1); also elsewhere on the board
QSPI_SD2: U7.3 (WP_IO2); also elsewhere on the board
QSPI_SD3: U7.7 (HOLD_IO3); also elsewhere on the board
QSPI_SS: R407.2, R408.1, U7.1 (CS_N); also elsewhere on the board
XIN: C425.1, Y1.1; also elsewhere on the board
XOUT: R409.1; also elsewhere on the board
XOUT_DAMPED: C426.1, R409.2, Y1.3

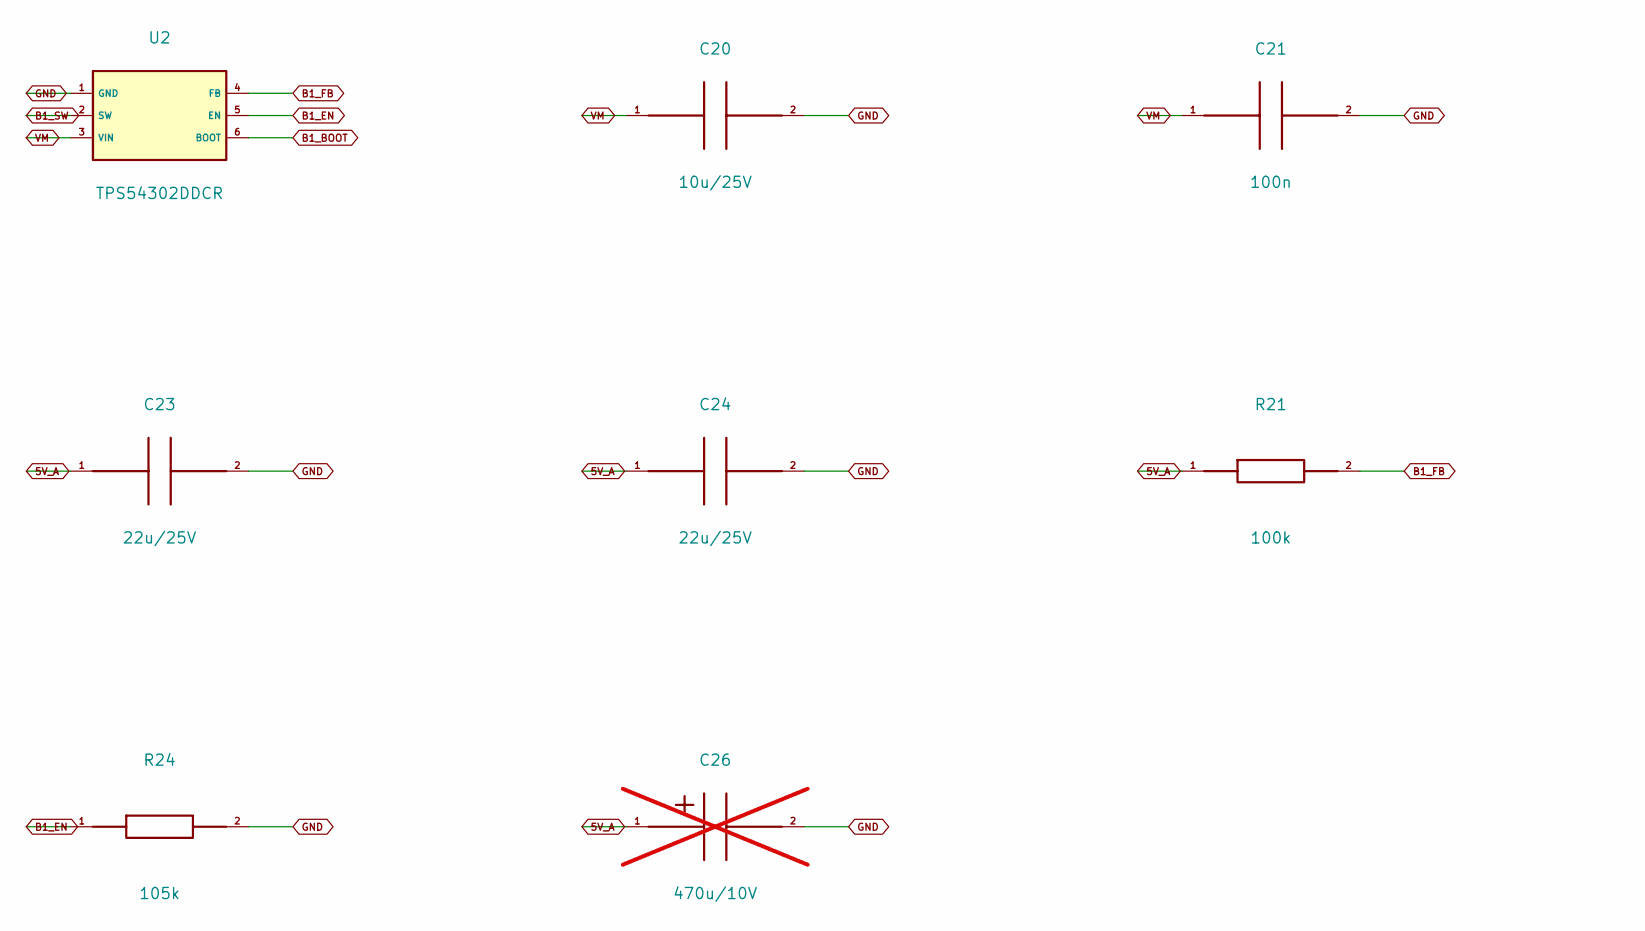
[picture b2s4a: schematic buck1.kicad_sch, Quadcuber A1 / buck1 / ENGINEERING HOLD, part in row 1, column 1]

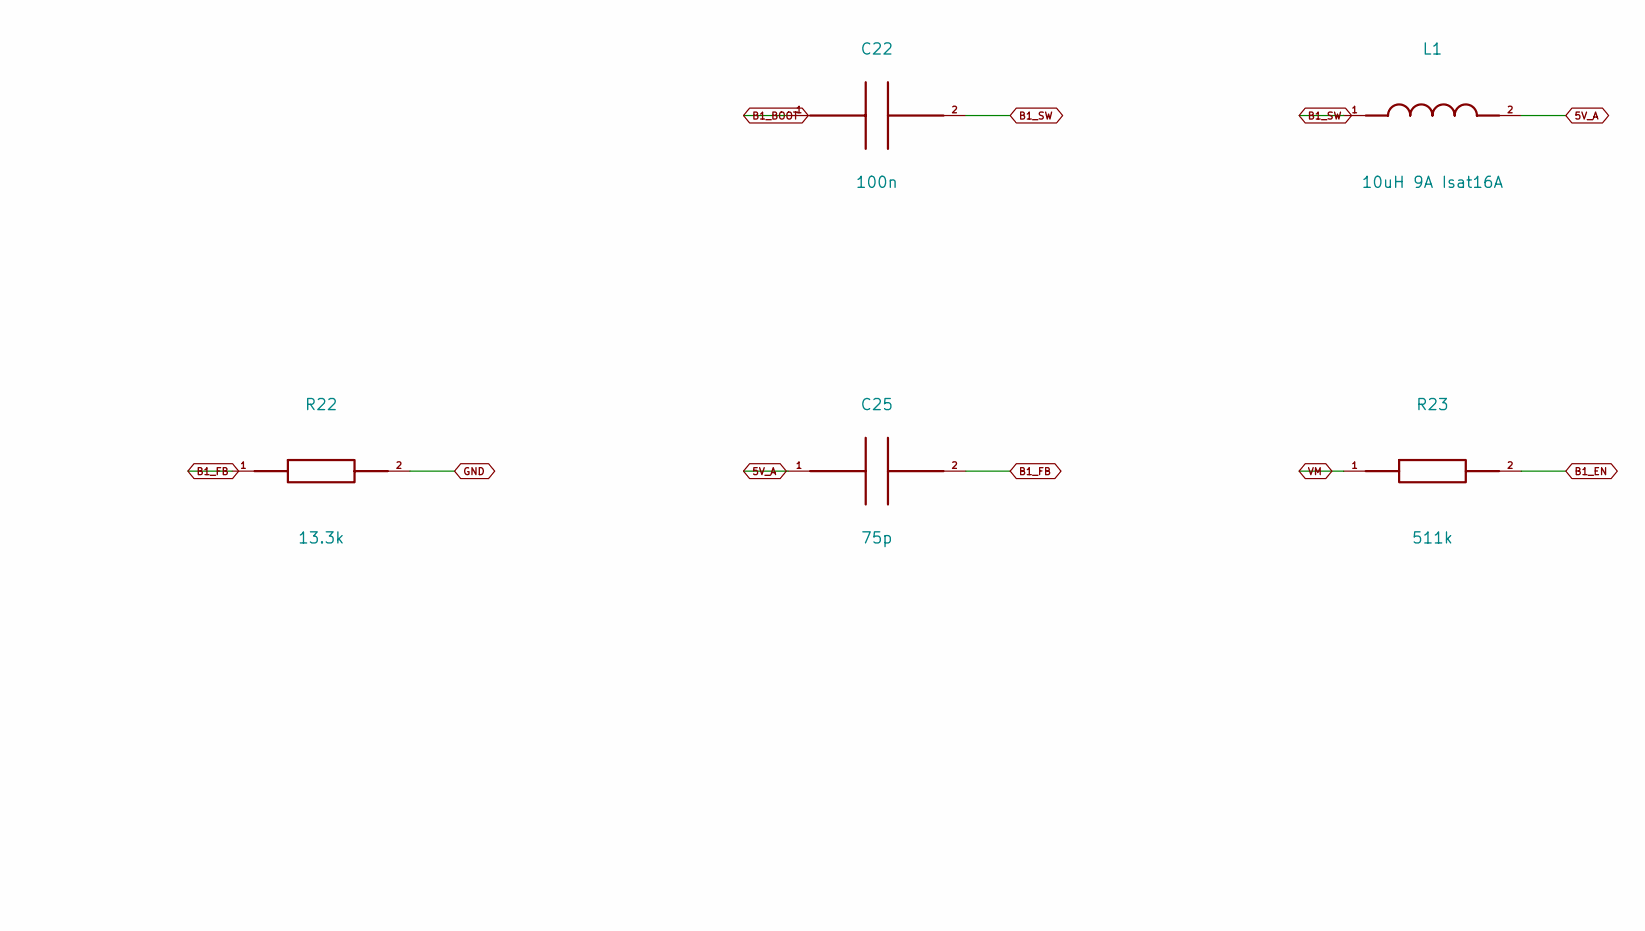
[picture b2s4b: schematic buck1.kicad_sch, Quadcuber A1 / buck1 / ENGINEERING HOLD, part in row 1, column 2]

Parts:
C20: 10u/25V; C_1210_3225Metric; MPN GRM32DR71E106KA12L
C21, C22: 100n; C_0805_2012Metric; MPN GRM21BR71H104KA01L
C23, C24: 22u/25V; C_1210_3225Metric; MPN GRM32ER71E226KE15L
C25: 75p; C_0603_1608Metric; MPN C0603C750J5GACTU
C26: 470u/10V; CP_Radial_D8.0mm_P3.50mm; MPN EEU-FR1A471; not fitted
L1: 10uH 9A Isat16A; L_Bourns_SRP1245A; MPN SRP1245A-100M
R21: 100k; R_0603_1608Metric; MPN RT0603BRD07100KL
R22: 13.3k; R_0603_1608Metric; MPN RT0603BRD0713K3L
R23: 511k; R_0603_1608Metric; MPN RC0603FR-07511KL
R24: 105k; R_0603_1608Metric; MPN RC0603FR-07105KL
U2: TPS54302DDCR; SOT-23-6; MPN TPS54302DDCR

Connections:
5V_A: C23.1, C24.1, C25.1, C26.1 (+), L1.2, R21.1; also elsewhere on the board
B1_BOOT: C22.1, U2.6 (BOOT)
B1_EN: R23.2, R24.1, U2.5 (EN)
B1_FB: C25.2, R21.2, R22.1, U2.4 (FB)
B1_SW: C22.2, L1.1, U2.2 (SW)
GND: C20.2, C21.2, C23.2, C24.2, C26.2 (-), R22.2, R24.2, U2.1 (GND); also elsewhere on the board
VM: C20.1, C21.1, R23.1, U2.3 (VIN); also elsewhere on the board
